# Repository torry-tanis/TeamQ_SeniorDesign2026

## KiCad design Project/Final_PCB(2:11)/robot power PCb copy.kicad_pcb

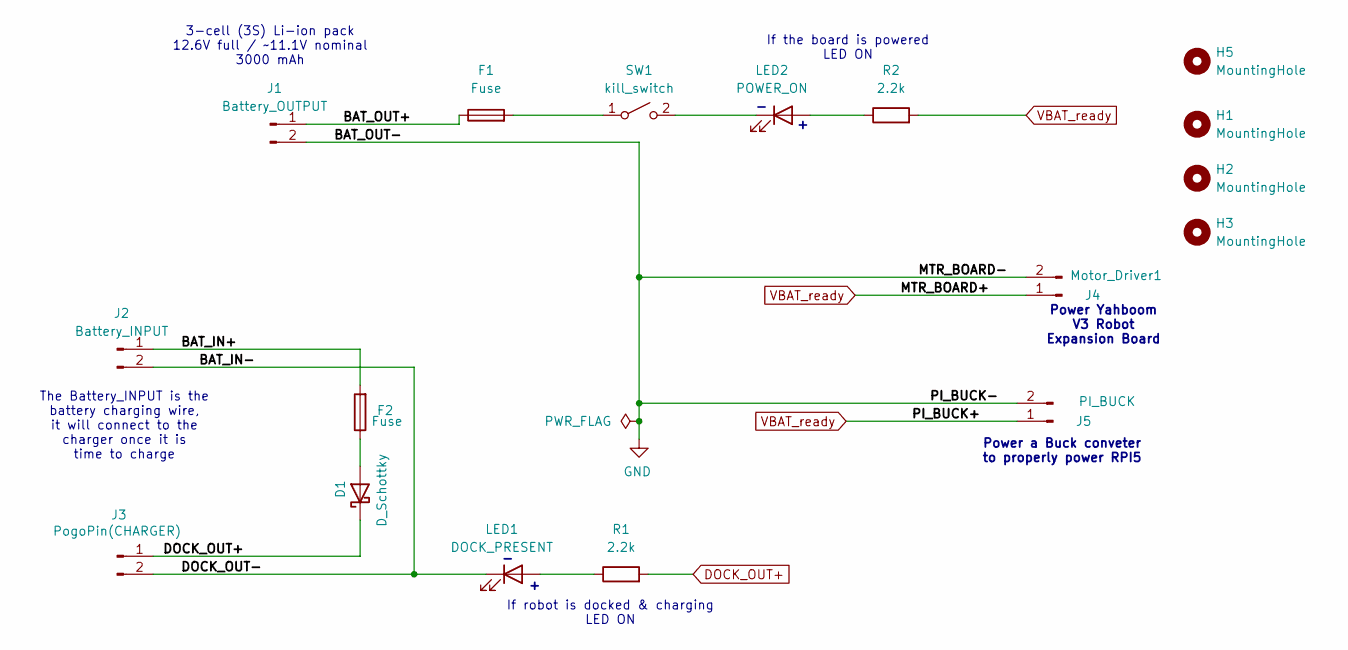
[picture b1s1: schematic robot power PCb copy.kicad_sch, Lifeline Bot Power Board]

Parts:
D1: D_Schottky; D_5KPW_P12.70mm_Horizontal
F1, F2: Fuse; Fuse_BelFuse_0ZRE0005FF_L8.3mm_W3.8mm
H1, H2, H3, H5: MountingHole; MountingHole_2.1mm
J1: Battery_OUTPUT; TerminalBlock_Phoenix_MKDS-1,5-2-5.08_1x02_P5.08mm_Horizont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
J2: Battery_INPUT; TerminalBlock_Phoenix_MKDS-1,5-2-5.08_1x02_P5.08mm_Horizont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
J3: PogoPin(CHARGER); TerminalBlock_Phoenix_MKDS-1,5-2-5.08_1x02_P5.08mm_Horizont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
J4: Motor_Driver1; TerminalBlock_Phoenix_MKDS-1,5-2-5.08_1x02_P5.08mm_Horizont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
J5: PI_BUCK; TerminalBlock_Phoenix_MKDS-1,5-2-5.08_1x02_P5.08mm_Horizont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
LED1: DOCK_PRESENT; LED_D3.0mm
LED2: POWER_ON; LED_D3.0mm
R1, R2: 2.2k; R_Axial_DIN0204_L3.6mm_D1.6mm_P7.62mm_Horizontal
SW1: kill_switch; TerminalBlock_Phoenix_MKDS-1,5-2-5.08_1x02_P5.08mm_Horizont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

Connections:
/BAT_IN+: F2.2, J2.1
/BAT_IN-: J2.2, J3.2, LED1.1 (K)
/BAT_OUT+: F1.1, J1.1
DOCK_OUT+: D1.1 (K), J3.1, R1.2
GND: J1.2, J4.2, J5.2
unnamed: D1.2 (A), F2.1
unnamed: LED1.2 (A), R1.1
unnamed: LED2.2 (A), R2.1
unnamed: LED2.1 (K), SW1.2 (B)
unnamed: F1.2, SW1.1 (A)
VBAT_ready: J4.1, J5.1, R2.2

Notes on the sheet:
Power Yahboom V3 Robot Expansion Board
The Battery_INPUT is the battery charging wire, it will connect to the charger once it is time to charge
If the board is powered LED ON
Power a Buck conveter to properly power RPI5
3-cell (3S) Li-ion pack 12.6V full / ~11.1V nominal 3000 mAh
If robot is docked & charging LED ON

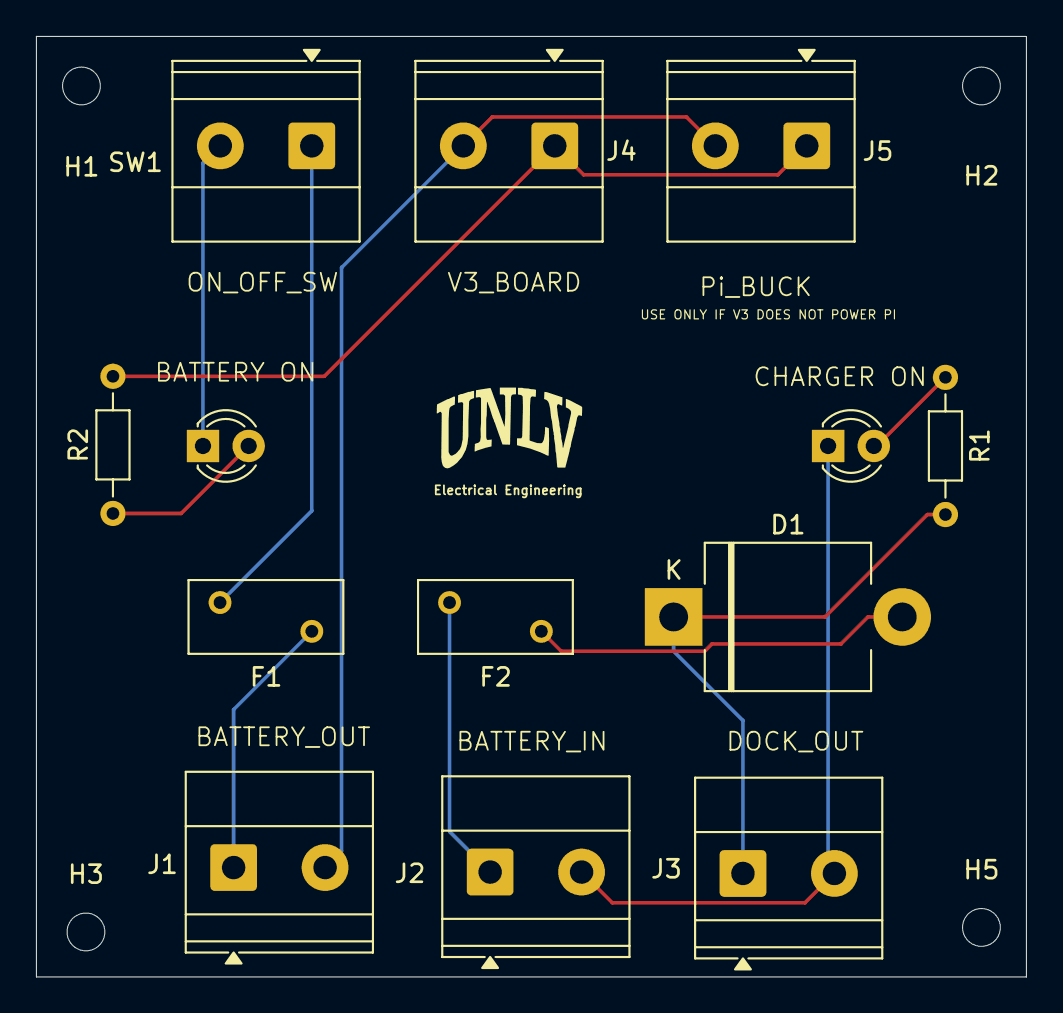
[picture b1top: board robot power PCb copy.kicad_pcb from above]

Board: 2 copper layers, 55.0 x 52.2 mm, 17 parts (0 on the bottom side), 11 nets.

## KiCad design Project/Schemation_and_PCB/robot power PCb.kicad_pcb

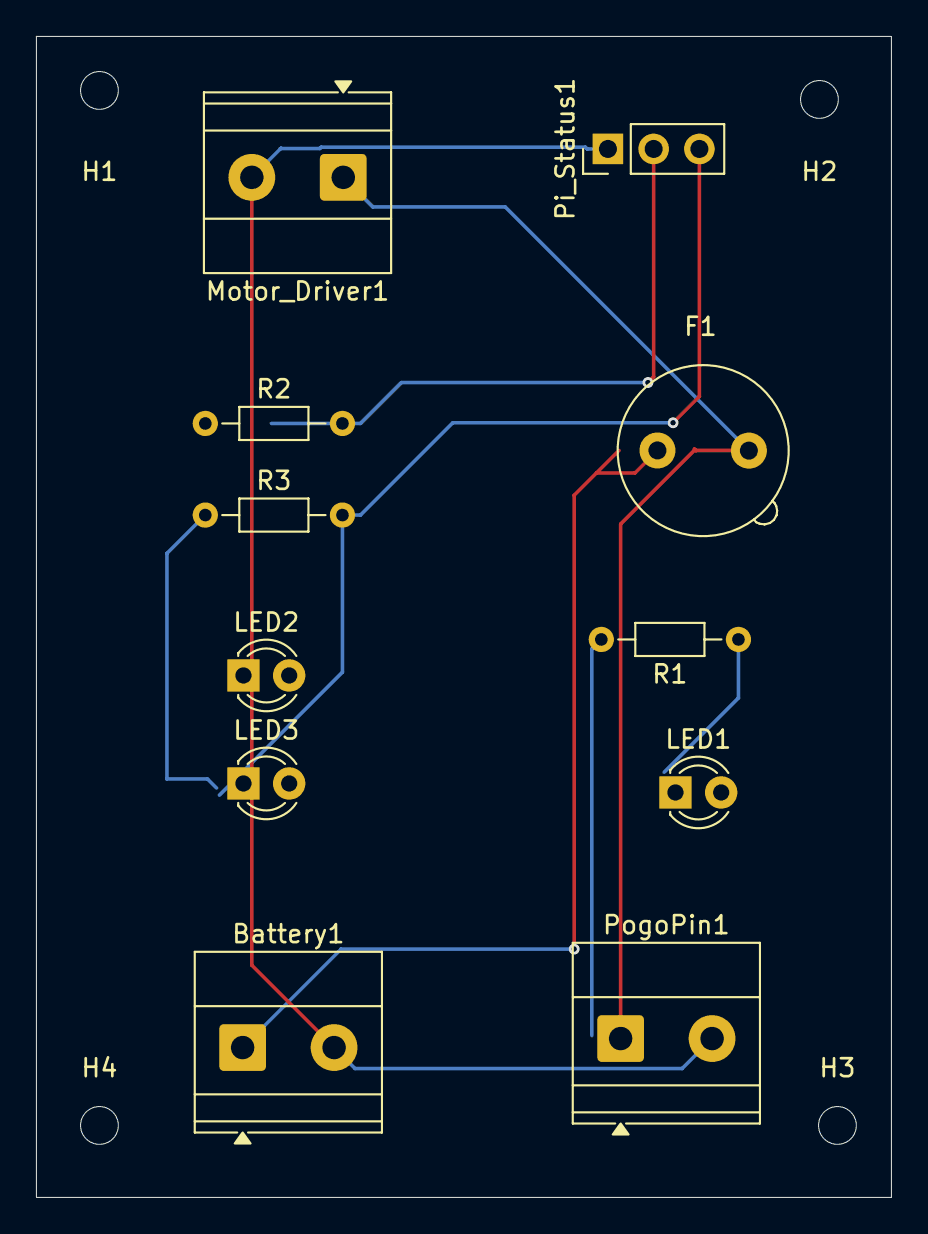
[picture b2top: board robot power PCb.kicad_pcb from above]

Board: 2 copper layers, 47.5 x 64.5 mm, 15 parts (0 on the bottom side), 5 nets.

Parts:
Battery1: Conn_01x02_Pin; TerminalBlock_Phoenix_MKDS-1,5-2-5.08_1x02_P5.08mm_Horizont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
F1: Fuse; Fuseholder_TR5_Littelfuse_No560_No460
H1, H2, H3, H4: MountingHole_Pad; MountingHole_2.1mm
LED1, LED2: LED; LED_D3.0mm
LED3: LED; LED_D3.0mm_Clear
Motor_Driver1: Conn_01x02_Pin; TerminalBlock_Phoenix_MKDS-1,5-2-5.08_1x02_P5.08mm_Horizont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
Pi_Status1: Conn_01x03_Pin; PinHeader_1x03_P2.54mm_Vertical
PogoPin1: Conn_01x02_Pin; TerminalBlock_Phoenix_MKDS-1,5-2-5.08_1x02_P5.08mm_Horizont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
R1, R2, R3: 1k; R_Axial_DIN0204_L3.6mm_D1.6mm_P7.62mm_Horizontal

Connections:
GND: Battery1.2, Motor_Driver1.2, Pi_Status1.1, PogoPin1.2
LED_GREEN_CTRL: Pi_Status1.3, R3.2
LED_RED_CTRL: Pi_Status1.2, R2.2
unnamed: Battery1.1, F1.1
VBAT: F1.2, Motor_Driver1.1, PogoPin1.1
